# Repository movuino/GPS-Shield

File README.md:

# GPS-Shield
GPS Shield for Movuino V0.99.3

Hardware is based on Quectel L86 GNSS 

Works on MovuinoESP32 v0.99.3 

Code requirements : 

install tinyGPS++ library from https://github.com/mikalhart/TinyGPSPlus

Examples are based on : https://github.com/ThaiEasyElec/ETEE068_L86_GPS_Examples

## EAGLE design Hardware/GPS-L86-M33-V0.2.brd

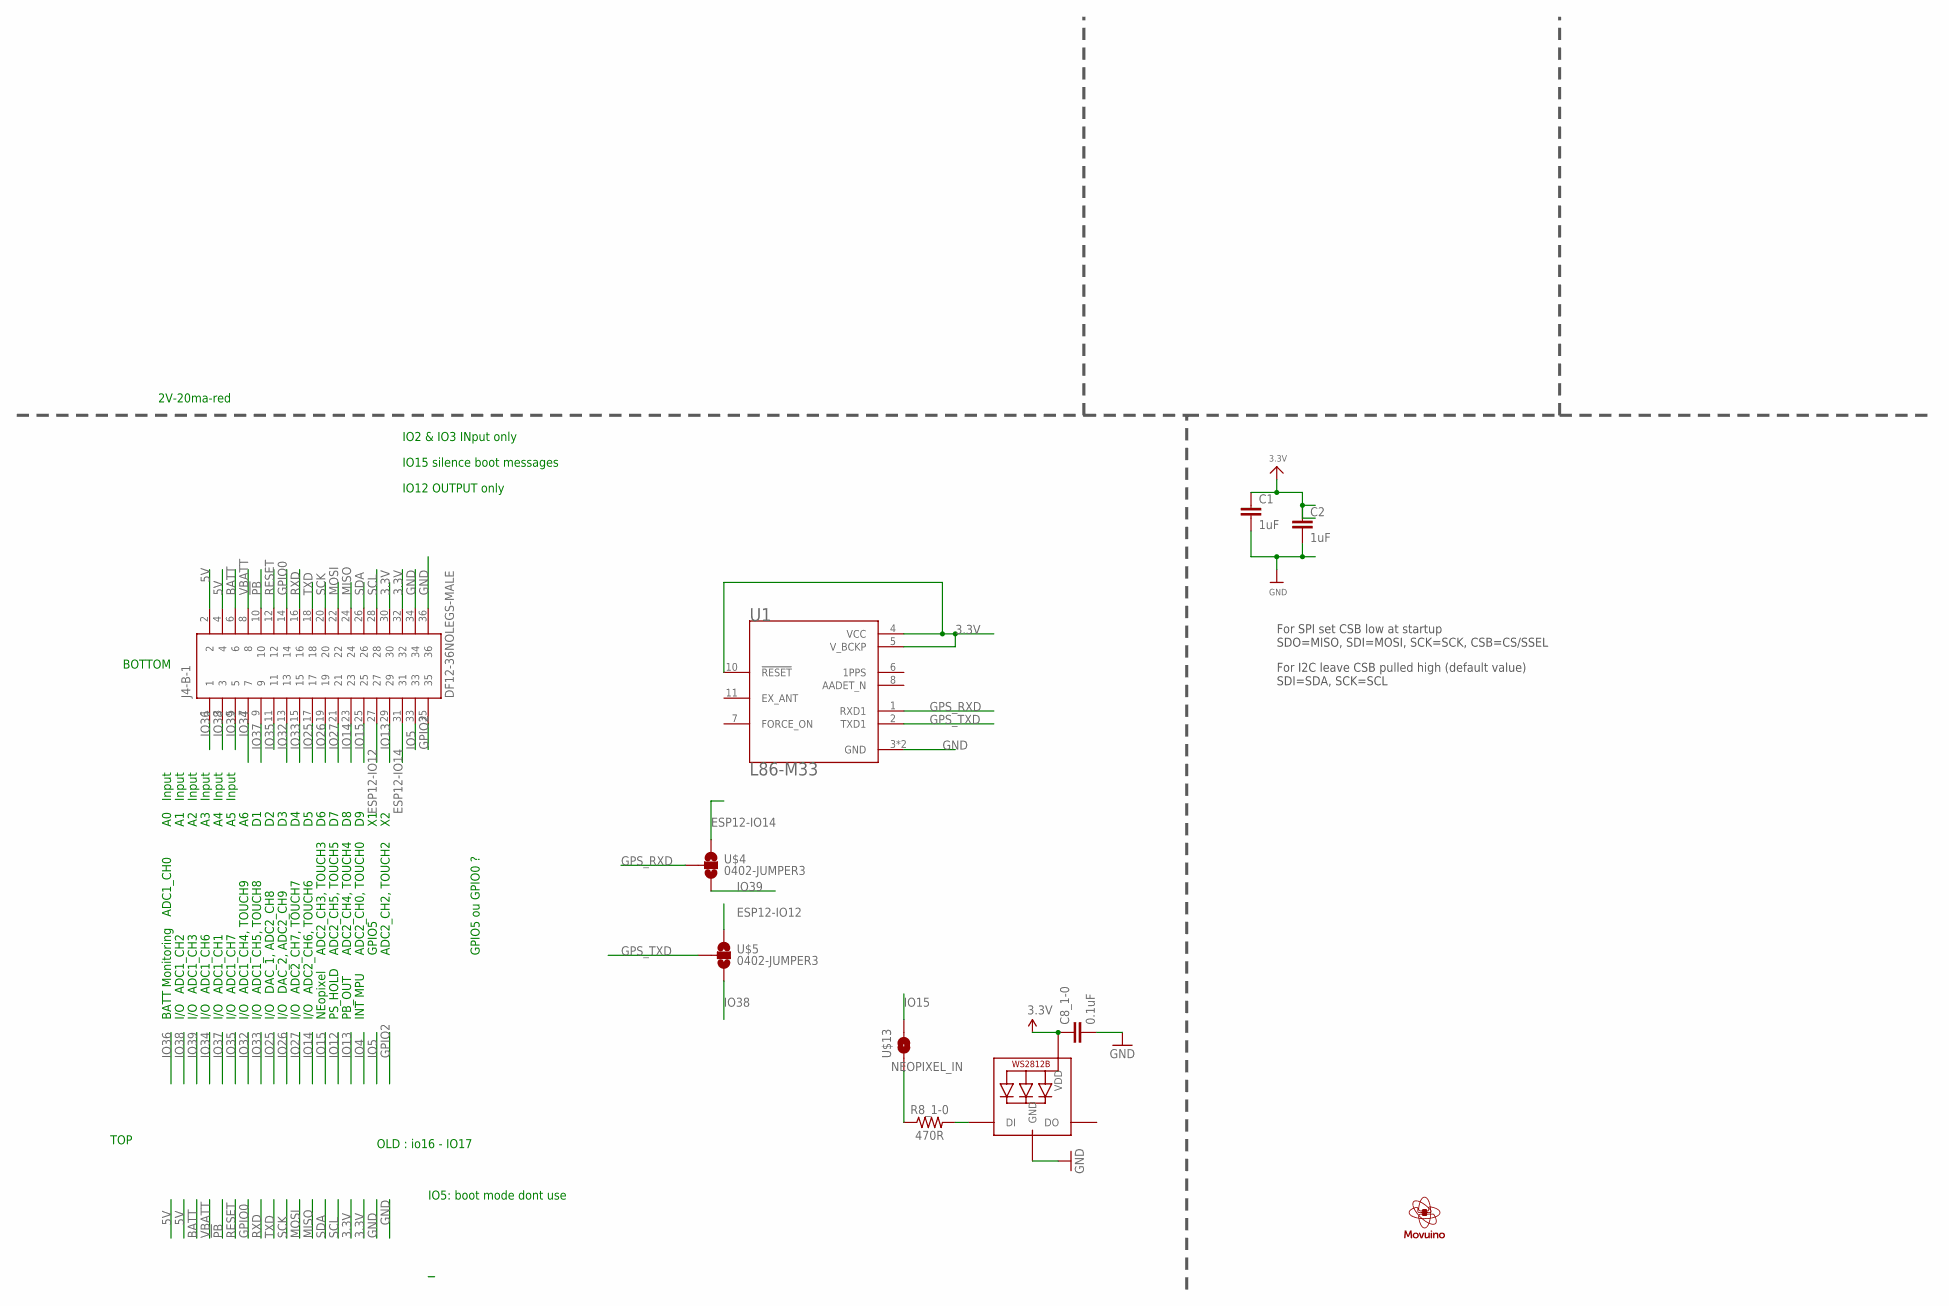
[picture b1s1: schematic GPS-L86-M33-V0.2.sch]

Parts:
C1, C2: 1uF; 0402-CAP
C8_1-0: 0.1uF; 0402-CAP
J4-B-1: DF12-36NOLEGS-MALE; DF12-36-DP-NL
LED1-0: WS2812B3535; LED3535
R8_1-0: 470R; R0402-SMALL-TDOCU
U1: L86-M33; XCVR_L86-M33
U$1: LOGO_MOVUINOTOP; LOGO_MOVUINO_BMP_10MM
U$4, U$5: 0402-JUMPER3; SJ_3
U$13: 0402-JUMPERCLOSED-DEFAULT; 0402-JUMPER-CLOSED

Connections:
3.3V: C1.1, C2.1, C8_1-0.1, J4-B-1.30, J4-B-1.32, LED1-0.2 (VDD), U1.4 (VCC), U1.5 (V_BCKP), U1.10 (!RESET)
5V: J4-B-1.2, J4-B-1.4
!PB!: J4-B-1.10
BATT: J4-B-1.6
ESP12-IO12: J4-B-1.27, U$5.1
ESP12-IO14: J4-B-1.31, U$4.1
GND: C1.2, C2.2, C8_1-0.2, J4-B-1.34, J4-B-1.36, LED1-0.4 (GND), U1.3 (GND), U1.12 (GND)
GPIO0: J4-B-1.14
GPIO2: J4-B-1.35
GPS_RXD: U1.1 (RXD1), U$4.2
GPS_TXD: U1.2 (TXD1), U$5.2
IO5: J4-B-1.33
IO13: J4-B-1.29
IO14: J4-B-1.23
IO15: J4-B-1.25, U$13.2
IO25: J4-B-1.17
IO26: J4-B-1.19
IO27: J4-B-1.21
IO32: J4-B-1.13
IO33: J4-B-1.15
IO34: J4-B-1.7
IO35: J4-B-1.11
IO36: J4-B-1.1
IO37: J4-B-1.9
IO38: J4-B-1.3, U$5.3
IO39: J4-B-1.5, U$4.3
MISO: J4-B-1.24
MOSI: J4-B-1.22
unnamed: LED1-0.1 (DI), R8_1-0.2
NEOPIXEL_IN: R8_1-0.1, U$13.1
RESET: J4-B-1.12
RXD: J4-B-1.16
SCK: J4-B-1.20
SCL: J4-B-1.28
SDA: J4-B-1.26
TXD: J4-B-1.18
VBATT: J4-B-1.8

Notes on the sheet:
IO12 OUTPUT only
IO2 & IO3 INput only
IO15 silence boot messages
TOP
BOTTOM
INT MPU
PB_OUT
NEopixel
PS_HOLD
OLD : io16 - IO17
I/O
BATT Monitoring
ADC1_CH6
ADC1_CH0
ADC1_CH2
ADC1_CH3
ADC1_CH1
ADC1_CH7
ADC1_CH4, TOUCH9
ADC1_CH5, TOUCH8
DAC_1, ADC2_CH8
DAC_2, ADC2_CH9
ADC2_CH7, TOUCH7
ADC2_CH6, TOUCH6
ADC2_CH0, TOUCH0
ADC2_CH5, TOUCH5
ADC2_CH4, TOUCH4
GPIO5
ADC2_CH3, TOUCH3
IO5: boot mode dont use
ADC2_CH2, TOUCH2
GPIO5 ou GPIO0 ?
Input
2V-20ma-red
For SPI set CSB low at startup SDO=MISO, SDI=MOSI, SCK=SCK, CSB=CS/SSEL
For I2C leave CSB pulled high (default value) SDI=SDA, SCK=SCL

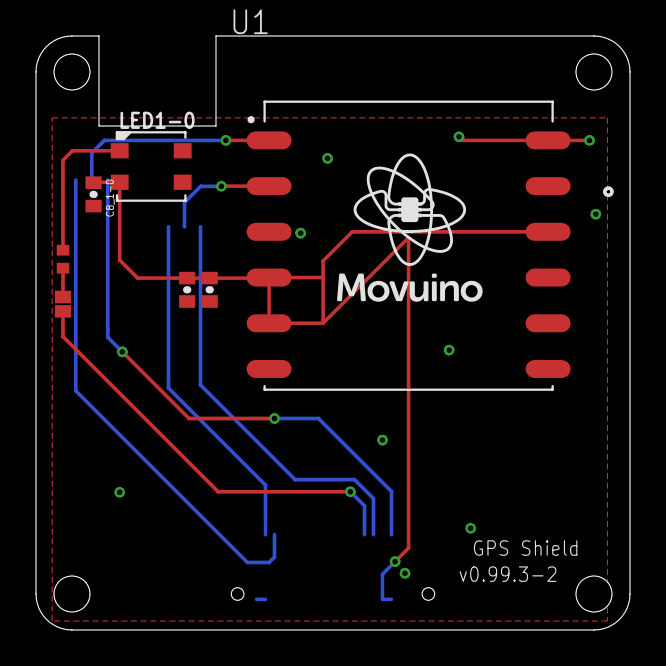
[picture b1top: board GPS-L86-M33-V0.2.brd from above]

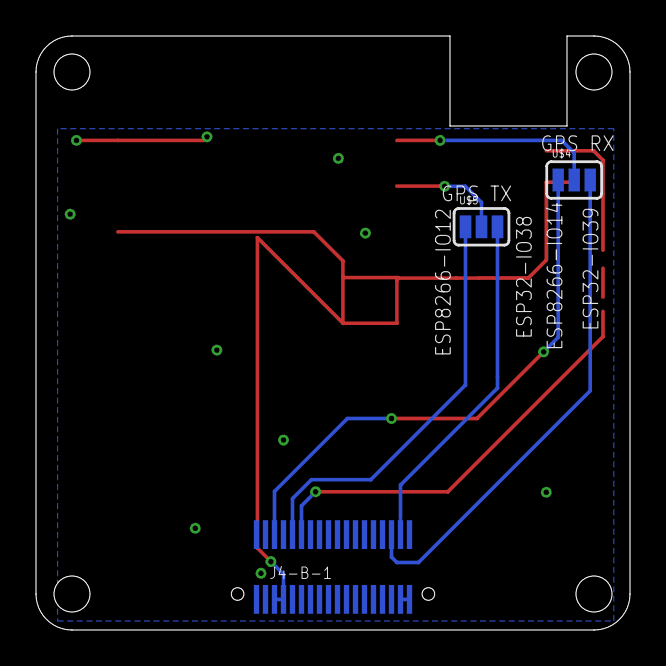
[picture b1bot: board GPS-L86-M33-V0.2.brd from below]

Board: 2 copper layers, 33.0 x 33.0 mm, 11 parts (3 on the bottom side), 12 nets.

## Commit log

2020-12-02 added hardware files and code examples
2021-01-17 added gerber file
2021-02-24 adding esp8266 gps
2021-02-24 added esp8266 support + neopixel

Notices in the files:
parts and their libraries:
SparkFun-Aesthetics: Licensing: CC v3.0 Share-Alike You are welcome to use this library for commercial purposes.
